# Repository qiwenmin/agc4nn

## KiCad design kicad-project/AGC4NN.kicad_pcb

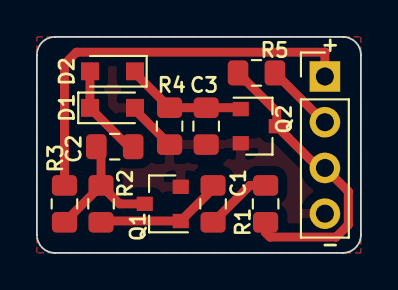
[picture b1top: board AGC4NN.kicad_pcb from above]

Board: 2 copper layers, 18.0 x 12.0 mm, 13 parts (0 on the bottom side), 9 nets.

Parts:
C1, C2: 0.1u; C_0805_2012Metric_Pad1.15x1.40mm_HandSolder
C3: 10u; C_0805_2012Metric_Pad1.15x1.40mm_HandSolder
D1, D2: 1N4148WS; D_SOD-323_HandSoldering
J1: Conn_01x04; PinHeader_1x04_P2.54mm_Vertical
Q1: MMBT3904; SOT-23
Q2: 2N7002; SOT-23
R1: 4.7K; R_0805_2012Metric_Pad1.15x1.40mm_HandSolder
R2: 470K; R_0805_2012Metric_Pad1.15x1.40mm_HandSolder
R3, R5: 2.2K; R_0805_2012Metric_Pad1.15x1.40mm_HandSolder
R4: 1M; R_0805_2012Metric_Pad1.15x1.40mm_HandSolder

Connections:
AF_IN: J1.2, R5.1
AF_OUT: J1.3, Q2.3, R1.2, R5.2
GND: C3.2, D1.2, J1.4, Q1.2, Q2.2, R4.2
unnamed: C1.1, R1.1
unnamed: C1.2, Q1.1, R2.2
unnamed: C2.1, D1.1, D2.2
unnamed: C2.2, Q1.3, R2.1, R3.2
unnamed: C3.1, D2.1, Q2.1, R4.1
VCC: J1.1, R3.1

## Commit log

2019-12-31 Initial commit.
2020-01-01 Make a new PCB layout. Upgrade to v01.c.
2020-01-01 Fix height: 12.001 -> 12.000
2020-01-06 Add XI logo to PCB.
2020-01-08 Change JLC... size to 0.8x0.8x0.15
